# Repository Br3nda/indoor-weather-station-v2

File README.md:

# indoor-weather-station-v2
Software for VCW indoor weatherstation

## Licensing

This software is GPL 3.0.

Included is driver software - HTS221 and LPS25 drivers, with their own copyrights
they have been released by their author, Amel Technology, under the LGPL2.1 license

	https://github.com/ameltech/sme-hts221-library
	https://github.com/ameltech/sme-lps25h-library

Our minor changes to these files are also released under LGPL2.1

---------------------------------------------------------------

## Data compression formats:

###humidity/temp compression - humidity is 7 bits 0-100, temp is 8 bits signed C
```
if bit 7 of byte 0 is 1 then bits 6:0 of byte0 is % humidity, byte1 is temp in C
if bit 7 of byte 0 is 0 then bits 6:4 are a signed diff of humidity from previous value, 3:0 are a signed diff of temp from previous value
if bits 7:4 of byte 0 are 1111 it is an escape (see below)
```
 
###pressure compression
```
if bit 0 of byte0 is set bits 6:0 are a signed delta of the pressure in kPa
if bit 1 of byte0 is set bits 6:0 of byte0 is MSB of pressure, byte 1 is LSB of pressure in kPa
if bits 7:4 of byte 0 are 1111 it is an escape (see below)
```

###escapes
```
1111 1111 - end of stream (unwritten FLASH)
1111 0000 - time signature
1111 0001 - time signature + change following samples to temp/humidity only (first following sample will be a full sample)
1111 0010 - time signature + change following samples to pressure only (first following sample will be a full sample)
1111 0011 - time signature + change following samples to temp/humidity followed by pressure (first following sample will be a full sample)
1111 0100 - followed by 2 bytes MSB LSB, sampling rate in seconds (default is 60 seconds, one sample per minute)
1111 0101 - followed by 0 terminated string comment
1111 0110 - followed by a 1-byte value - 'mark' a user inserted mark in the stream (for example "I turned on the heater here")
1111 0111 - null - ignored for padding
1111 1000 - followed by 1-byte count 1-255 - previous value didn't change to N samples
1111 1001 - 1110 undefined
```

###time signature:
```
byte0 - bits 7:0 years since 2000 0-254 - value '0xff' means no time is known (bytes1-4 are missing)
byte1 - bits 7:4 month 1-12,  bits 3:0 day MSB 1-31
byte2 - bit 7 day LSB 1-23, bits 6:2 hour 0-23 bits 1:0 minutes msb
byte3 - bits 7:4 minutes lsb 0-59, bits 3:0 - F means byte4 not included, otherwise undefined, set to 0
byte4 - bits 7:6 undefined set to 0, bits 5:0 seconds
```

---------------------------------------------------------------

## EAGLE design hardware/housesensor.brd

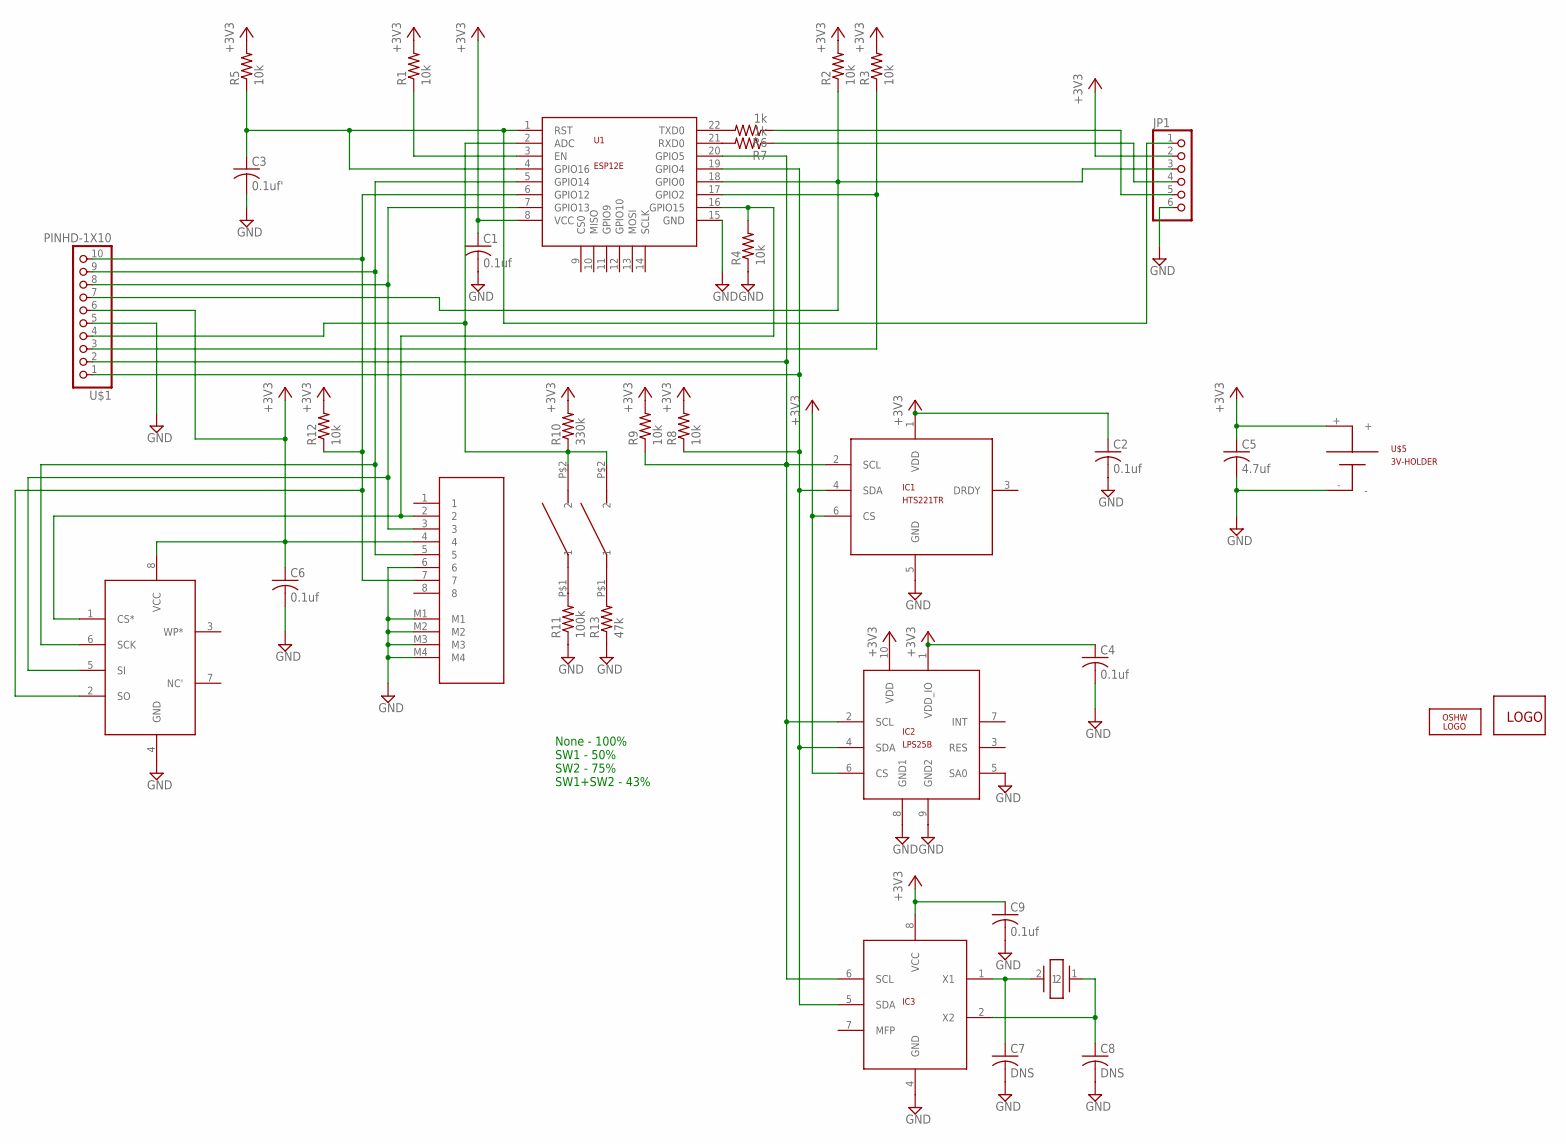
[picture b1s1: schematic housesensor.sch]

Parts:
C1, C2, C4, C6, C9: 0.1uf; C0603
C3: 0.1uf'; C0603
C5: 4.7uf; C1206
C7, C8: DNS; C0603
IC1: HTS221TR; HTS221
IC2: LPS25B; LPS25
IC3: MCP7940MS08M; SO8M
IC4: SPI-FLASH; SO8J
JP1: PINHD-1X6; 1X06
LOGO1: OSHW_LOGO_FILLX0150-NT; OSHW_FILLX150_NOTEXT
R1, R2, R3, R4, R5, R8, R9, R12: 10k; R0603
R6, R7: 1k; R0603
R10: 330k; R0603
R11: 100k; R0603
R13: 47k; R0603
SW1, SW2: RED-SWITCH; SW2
U1: ESP12E; ESP8266-SMD
U$1: PINHD-1X10; 1X10-BIG
U$4: MICRO-SD-SCHD1A0101; MICROSD-P
U$5: 3V-HOLDER
U$6: MOONBASE-LOGO
X1: 32KHZ

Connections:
+3V3: C1.1, C2.1, C4.1, C5.1, C6.1, C9.1, IC1.1 (VDD), IC1.6 (CS), IC2.1 (VDD_IO), IC2.6 (CS), IC2.10 (VDD), IC3.8 (VCC), IC4.8 (VCC), JP1.2, R1.2, R2.2, R3.2, R5.2, R8.2, R9.2, R10.2, R12.2, U1.8 (VCC), U$1.6, U$4.4, U$5.+
EN: R1.1, U1.3 (EN)
GND: C1.2, C2.2, C3.2, C4.2, C5.2, C6.2, C7.2, C8.2, C9.2, IC1.5 (GND), IC2.5 (SA0), IC2.8 (GND1), IC2.9 (GND2), IC3.4 (GND), IC4.4 (GND), JP1.6, R4.1, R11.1, R13.1, U1.15 (GND), U$1.5, U$4.6, U$4.M1, U$4.M2, U$4.M3, U$4.M4, U$5.-
GPIO0: JP1.3, R2.1, U1.18 (GPIO0), U$1.7
GPIO2: R3.1, U1.17 (GPIO2), U$1.3
GPIO12: IC4.2 (SO), R12.1, U1.6 (GPIO12), U$1.10, U$4.7
GPIO13: IC4.5 (SI), U1.7 (GPIO13), U$1.8, U$4.3
GPIO14: IC4.6 (SCK), U1.5 (GPIO14), U$1.9, U$4.5
GPIO15: IC4.1 (CS*), R4.2, U1.16 (GPIO15), U$4.2
unnamed: R11.2, SW1.P$1 (1)
unnamed: R10.1, SW1.P$2 (2), SW2.P$2 (2), U1.2 (ADC), U$1.4
unnamed: R13.2, SW2.P$1 (1)
unnamed: C8.1, IC3.2 (X2), X1.1
unnamed: C7.1, IC3.1 (X1), X1.2
unnamed: R6.2, U1.22 (TXD0)
unnamed: R7.2, U1.21 (RXD0)
unnamed: JP1.5, R6.1
unnamed: JP1.4, R7.1
RST: C3.1, JP1.1, R5.1, U1.1 (RST), U1.4 (GPIO16)
SCL: IC1.2 (SCL), IC2.2 (SCL), IC3.6 (SCL), R9.1, U1.20 (GPIO5), U$1.2
SDA: IC1.4 (SDA), IC2.4 (SDA), IC3.5 (SDA), R8.1, U1.19 (GPIO4), U$1.1

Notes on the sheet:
None - 100% SW1 - 50% SW2 - 75% SW1+SW2 - 43%

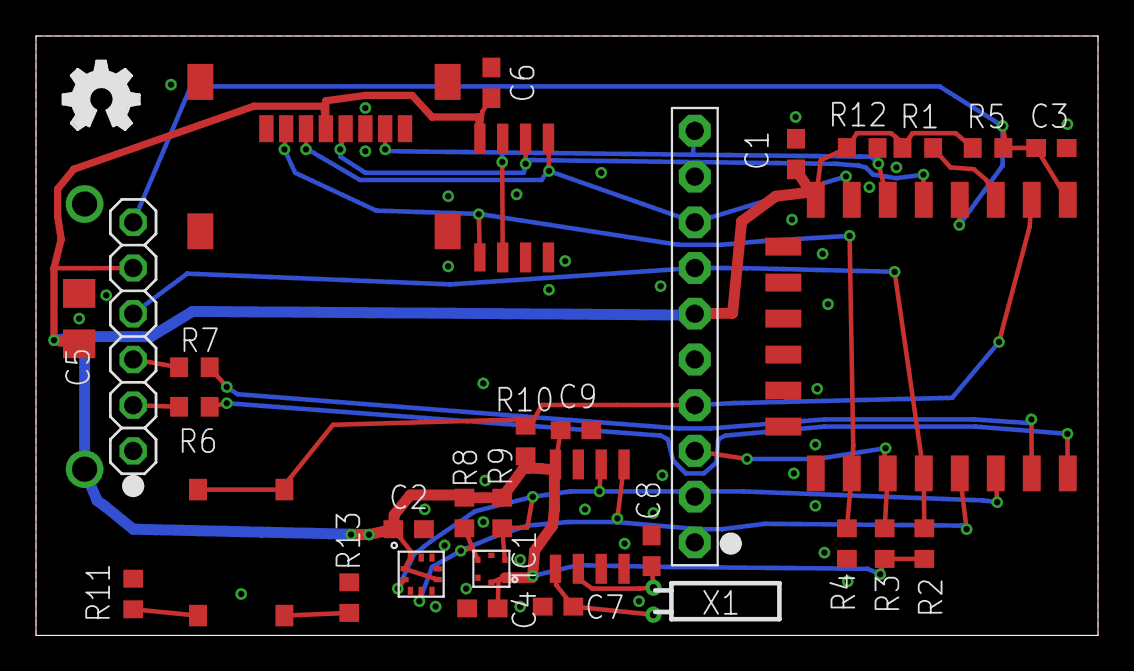
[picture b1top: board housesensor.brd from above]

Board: 2 copper layers, 59.0 x 33.3 mm, 36 parts (1 on the bottom side), 21 nets.

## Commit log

2016-09-07 update copyright info
2016-09-07 add compression documentation
2016-09-07 Add v1.0 hardware design files
2016-09-07 use markdown language
2016-09-07 more md changes
2016-09-15 Add basic support for buttons - mark stream
2016-09-15 Add sample code for Ian to fill in
2016-09-17 Integrated captive config.
2016-09-17 Blink LED when starting captive config.
2016-09-22 change html to work for us
2016-09-24 Starting DataUploader - just scaffold so far.
2016-09-24 Add .gitignore
2016-09-25 DataUploader can now connect to WiFi networks.
    It's really slow connecting to my home WiFi - not sure wi.
2016-09-25 Added a few comments
2016-10-06 add magic number so we can restart when we update code
2016-10-06 added defines for count/delay
2016-10-12 movce decompressor into its own file
2016-10-12 change compression to recognise that pressure doesn't change much
2016-10-12 remove trace
2016-10-12 added TODC write command looking forward to NTP support
2016-10-19 Reinstated DataUploader in house_sensor.ino.ino
2016-10-19 Handle missing WiFi network in DataUploader.
2016-10-19 Add connection timeout to DataUploader.
2016-10-19 Bit of work on uploading to a server.
2016-10-20 Add email address input to captive config
2016-10-20 add eeprom support
2016-10-22 redesign eeprom to avoid using extra space and making extra copies
2016-10-22 Reinstated DataUploader
2016-10-22 Implemented house_eeprom::changed()
2016-10-22 Fix uninitialized pointer in CaptiveConfig.
2016-10-22 More gracefully handle case where no APs are found
    Should also make sure the Captive Config UI looks OK.
2016-10-22 Store preferred WiFi SSID and passphrase in EEPROM
2016-10-23 add flash files
2016-10-27 Prep for registering on public WiFi
2016-10-30 Bring up flash
2016-11-07 Fix copy-and-paste error. Was using SSID for pass.
2016-11-13 Upload real data from flash.
2016-11-19 Fix buffer overrun in HomeFlash::LoadBuffer()
2016-11-19 Untested: Update next_page_offset state
2016-11-19 Fix memory leak when uploading data.
2017-03-25 Picking up work again

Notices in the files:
hardware/housesensor.brd:
(C) 2016
